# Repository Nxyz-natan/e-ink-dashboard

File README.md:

# e-ink-dashboard
e ink dashboard for me to display weather my room temp calander and date and time and disply my spotify 

Hardware Design

I designed a custom PCB that integrates:
ESP32-S3 microcontroller
BME280 sensor
Power management (voltage regulator + charging IC)
USB-C input
Display connector

Features

Real-time weather display
displays whats spotify playing
Room temperature and humidity using BME280 sensor
Calendar, date, and time display
Low power consumption using e-ink technology

here is my schematics 

here my pcb

here is my case 

## Bill of Materials

| Name | Purpose | Qty | Total Cost (USD) | Distributor |
|------|---------|-----|-----------------|-------------|
| 7.3" E Ink Spectra 6 Display 800x480 | Display | 1 | $47.34 | Good Display |
| Resistor 4.7kΩ 0402 | Resistor | 100 | $0.08 | LCSC |
| Pin Socket 1×08 2.54mm | Socket | 5 | $0.53 | LCSC |
|pcb | pcb | 5 | 3.50$ | jlcp |
| Switch 6×6×5mm | Button | 5 | $0.36 | LCSC |
| Resistor 1.2kΩ 0402 | Resistor | 100 | $0.09 | LCSC |
| BME280 | Temp/humidity sensor | 1 | $7.42 | LCSC |
| ME6211C33M5G-N | Voltage regulator | 10 | $0.50 | LCSC |
| TP4056-42-ESOP8 | Battery charger IC | 5 | $0.93 | LCSC |
| ESP32-S3-WROOM-1-N16R8 | MCU | 1 | $5.21 | LCSC |

**Total with shipping: 95.85$**

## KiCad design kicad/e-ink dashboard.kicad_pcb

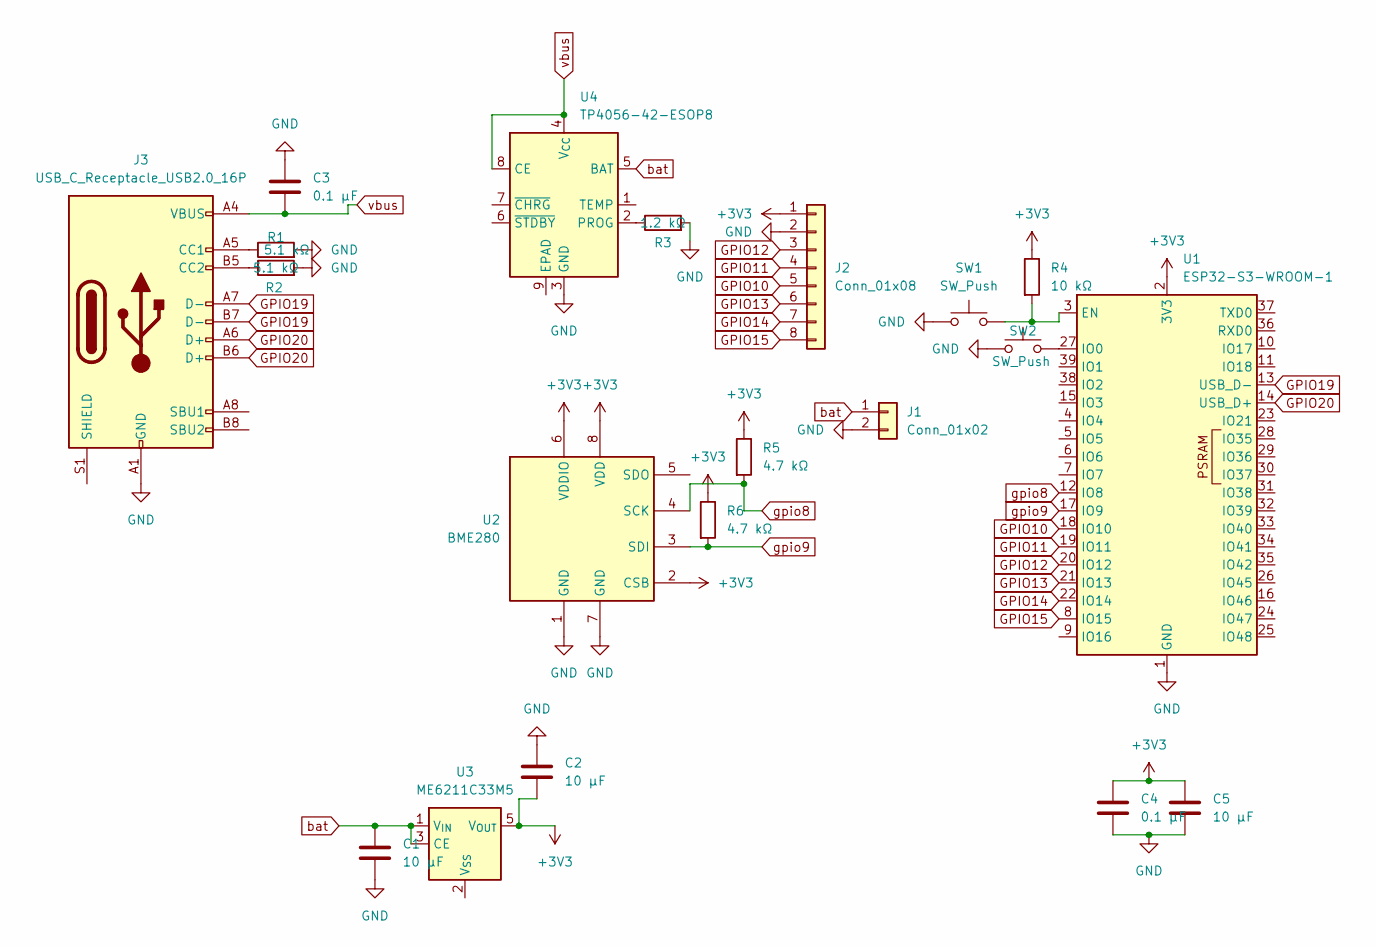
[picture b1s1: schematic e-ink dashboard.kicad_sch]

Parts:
C1, C2, C5: 10 µF; C_0603_1608Metric
C3, C4: 0.1 µF; C_0402_1005Metric
J1: Conn_01x02; JST_PH_B2B-PH-K_1x02_P2.00mm_Vertical
J2: Conn_01x08; PinSocket_1x08_P2.54mm_Vertical
J3: USB_C_Receptacle_USB2.0_16P; USB_C_Receptacle_HRO_TYPE-C-31-M-12
R1, R2: 5.1 kΩ; R_0402_1005Metric
R3: 1.2 kΩ; R_0805_2012Metric
R4: 10 kΩ; R_0603_1608Metric
R5, R6: 4.7 kΩ; R_0805_2012Metric
SW1, SW2: SW_Push; SW_Push_1TS009xxxx-xxxx-xxxx_6x6x5mm
U1: ESP32-S3-WROOM-1
U2: BME280; Bosch_LGA-8_2.5x2.5mm_P0.65mm_ClockwisePinNumbering
U3: ME6211C33M5; SOT-23-5
U4: TP4056-42-ESOP8; SOIC-8-1EP_3.9x4.9mm_P1.27mm_EP2.41x3.3mm_ThermalVias

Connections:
+3V3: C2.2, C4.1, C5.1, J2.1, R4.1, R5.1, R6.1, U1.2 (3V3), U2.2 (CSB), U2.6 (VDDIO), U2.8 (VDD), U3.5 (V_{OUT})
GND: C1.1, C2.1, C3.1, C4.2, C5.2, J1.2, J2.2, J3.A1 (GND), J3.A12 (GND), J3.B1 (GND), J3.B12 (GND), R1.2, R2.2, R3.2, SW1.1, SW2.1, U1.1 (GND), U1.40 (GND), U1.41 (GND), U2.1 (GND), U2.7 (GND), U4.3 (GND)
GPIO10: J2.5, U1.18 (IO10)
GPIO11: J2.4, U1.19 (IO11)
GPIO12: J2.3, U1.20 (IO12)
GPIO13: J2.6, U1.21 (IO13)
GPIO14: J2.7, U1.22 (IO14)
GPIO15: J2.8, U1.8 (IO15)
GPIO19: J3.A7 (D-), J3.B7 (D-), U1.13 (USB_D-)
GPIO20: J3.A6 (D+), J3.B6 (D+), U1.14 (USB_D+)
unnamed: J3.A5 (CC1), R1.1
unnamed: J3.B5 (CC2), R2.1
unnamed: R4.2, SW1.2, U1.3 (EN)
unnamed: SW2.2, U1.27 (IO0)
unnamed: R3.1, U4.2 (PROG)
bat: C1.2, J1.1, U3.1 (V_{IN}), U3.3 (CE), U4.5 (BAT)
gpio8: R5.2, U1.12 (IO8), U2.4 (SCK)
gpio9: R6.2, U1.17 (IO9), U2.3 (SDI)
vbus: C3.2, J3.A4 (VBUS), J3.A9 (VBUS), J3.B4 (VBUS), J3.B9 (VBUS), U4.4 (V_{CC}), U4.8 (CE)

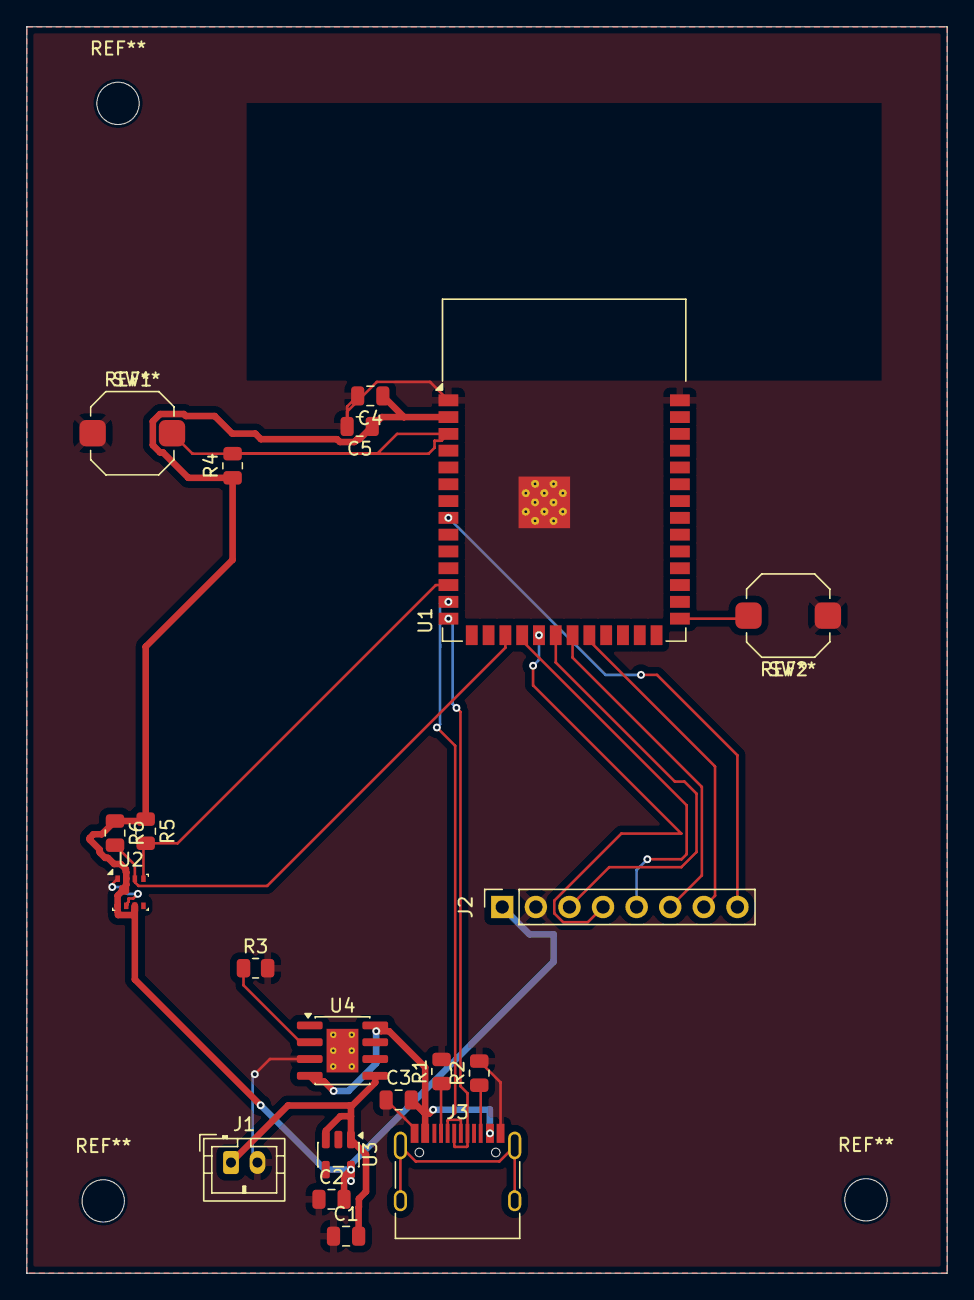
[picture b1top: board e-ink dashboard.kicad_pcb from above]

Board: 2 copper layers, 69.6 x 94.2 mm, 20 parts (0 on the bottom side), 19 nets.

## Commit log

2026-05-08 Rename e-ink dashboard.kicad_sch to kicad/e-ink dashboard.kicad_sch
2026-05-08 Rename e-ink dashboard.kicad_pro to kicad/e-ink dashboard.kicad_pro
2026-05-08 Rename e-ink dashboard.kicad_pcb to kicad/e-ink dashboard.kicad_pcb
2026-05-08 Rename Archive.zip to pcb production/Archive.zip
2026-05-08 Rename bottom case e ink.shapr to cad/bottom case e ink.shapr
2026-05-08 Rename case e ink.step to cad/case e ink.step
2026-05-08 Rename e ink dahsboard lid.step to cad/e ink dahsboard lid.step
2026-05-08 Rename new top.step to cad/new top.step
2026-05-08 Rename top lid e ink.shapr to cad/top lid e ink.shapr
2026-05-08 Rename e ink dashboard-bom-2.csv to BOM/e ink dashboard-bom-2.csv
